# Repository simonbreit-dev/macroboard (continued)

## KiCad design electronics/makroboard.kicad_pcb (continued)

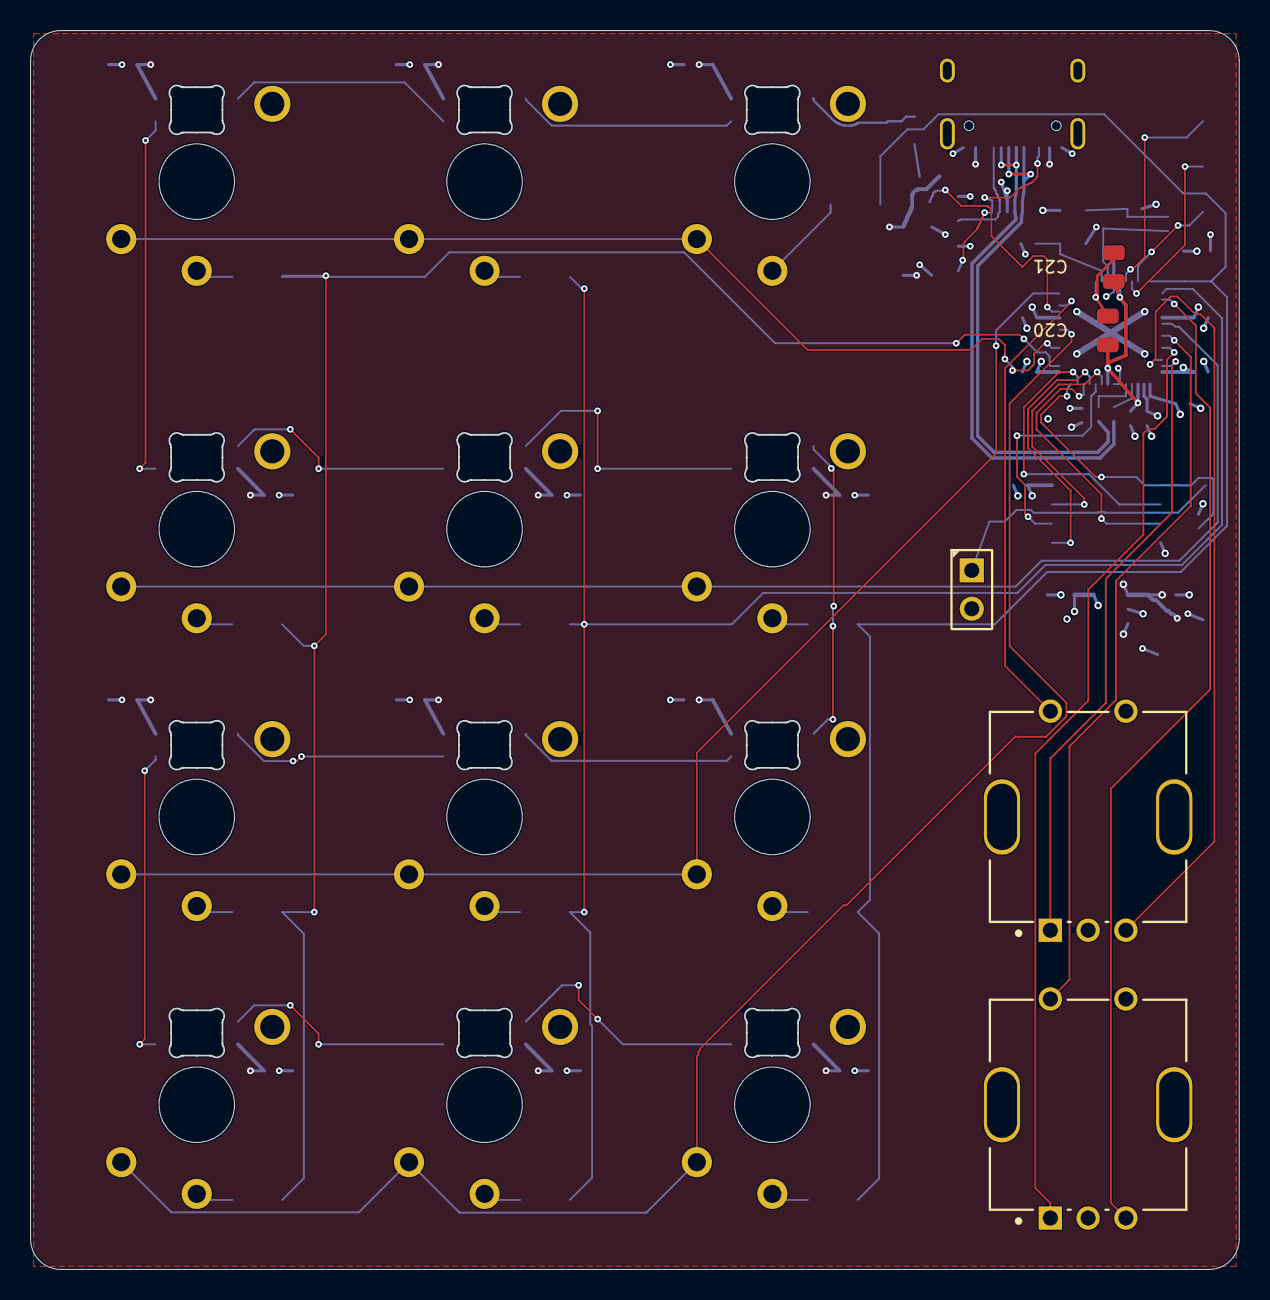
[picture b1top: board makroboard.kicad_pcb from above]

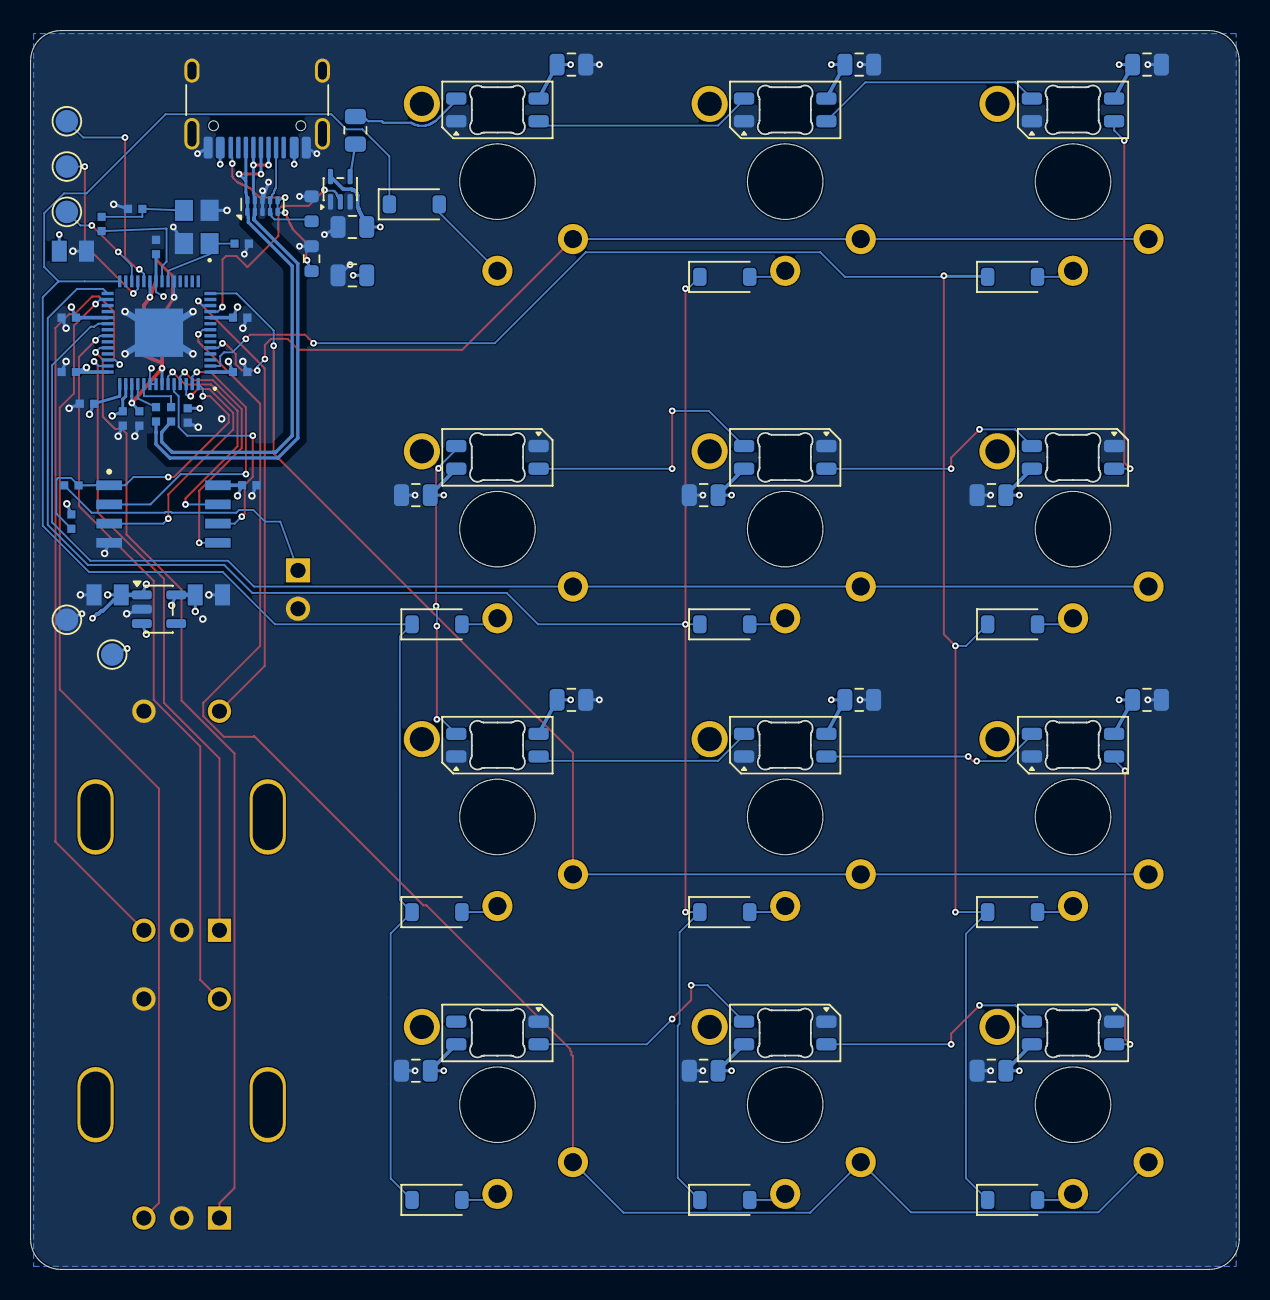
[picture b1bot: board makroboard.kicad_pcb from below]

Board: 4 copper layers, 80.0 x 82.0 mm, 90 parts (73 on the bottom side), 62 nets.

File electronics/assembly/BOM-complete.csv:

Designator,Value,Footprint,MPN,LCSC,Assembly
C1,100nF,Makroboard_PCB:C1_C_0805_2012Metric,CC0805KRX7R9BB104,C49678,Factory
C2,100nF,Makroboard_PCB:C2_C_0805_2012Metric,CC0805KRX7R9BB104,C49678,Factory
C3,100nF,Makroboard_PCB:C3_C_0805_2012Metric,CC0805KRX7R9BB104,C49678,Factory
C4,100nF,Makroboard_PCB:C4_C_0805_2012Metric,CC0805KRX7R9BB104,C49678,Factory
C5,100nF,Makroboard_PCB:C5_C_0805_2012Metric,CC0805KRX7R9BB104,C49678,Factory
C6,100nF,Makroboard_PCB:C6_C_0805_2012Metric,CC0805KRX7R9BB104,C49678,Factory
C7,100nF,Makroboard_PCB:C7_C_0805_2012Metric,CC0805KRX7R9BB104,C49678,Factory
C8,100nF,Makroboard_PCB:C8_C_0805_2012Metric,CC0805KRX7R9BB104,C49678,Factory
C9,100nF,Makroboard_PCB:C9_C_0805_2012Metric,CC0805KRX7R9BB104,C49678,Factory
C10,100nF,Makroboard_PCB:C10_C_0805_2012Metric,CC0805KRX7R9BB104,C49678,Factory
C11,100nF,Makroboard_PCB:C11_C_0805_2012Metric,CC0805KRX7R9BB104,C49678,Factory
C12,100nF,Makroboard_PCB:C12_C_0805_2012Metric,CC0805KRX7R9BB104,C49678,Factory
C13,100nF,Makroboard_PCB:C13_C_0805_2012Metric,CC0805KRX7R9BB104,C49678,Factory
C15,15p,Makroboard_PCB:C15_generic_capc1005x50,0402CG150J500NT,C1548,Factory
C16,15p,Makroboard_PCB:C16_generic_capc1005x50,0402CG150J500NT,C1548,Factory
C17,2.2uF,Makroboard_PCB:C17_generic_capc2012x125,CL21B225KOFNNNE,C28234,Factory
C18,10uF,Makroboard_PCB:C18_generic_capc2012x125,CL21A106KAYNNNE,C15850,Factory
C19,100n,Makroboard_PCB:C19_generic_capc1005x50,CL05B104KO5NNNC,C1525,Factory
C20,100nF,Makroboard_PCB:C20_C_0805_2012Metric,CC0805KRX7R9BB104,C49678,Factory (all-SMD) / required manual Top (one-side)
C21,100nF,Makroboard_PCB:C21_C_0805_2012Metric,CC0805KRX7R9BB104,C49678,Factory (all-SMD) / required manual Top (one-side)
C22,1u,Makroboard_PCB:C22_generic_capc1005x50,CL05A105KA5NQNC,C52923,Factory
C23,100n,Makroboard_PCB:C23_generic_capc1005x50,CL05B104KO5NNNC,C1525,Factory
C24,1u,Makroboard_PCB:C24_generic_capc1005x50,CL05A105KA5NQNC,C52923,Factory
C25,100n,Makroboard_PCB:C25_generic_capc1005x50,CL05B104KO5NNNC,C1525,Factory
C26,100n,Makroboard_PCB:C26_generic_capc1005x50,CL05B104KO5NNNC,C1525,Factory
C27,100n,Makroboard_PCB:C27_generic_capc1005x50,CL05B104KO5NNNC,C1525,Factory
C28,100n,Makroboard_PCB:C28_generic_capc1005x50,CL05B104KO5NNNC,C1525,Factory
C29,100n,Makroboard_PCB:C29_generic_capc1005x50,CL05B104KO5NNNC,C1525,Factory
C30,100n,Makroboard_PCB:C30_generic_capc1005x50,CL05B104KO5NNNC,C1525,Factory
C31,10u,Makroboard_PCB:C31_generic_capc2012x125,CL21A106KAYNNNE,C15850,Factory
C32,2.2uF,Makroboard_PCB:C32_C_0805_2012Metric,CL21B225KOFNNNE,C28234,Factory
D1,SK6812MINI-E,Makroboard_PCB:D1_LED_SK6812MINI-E_3.2x2.8mm_P1.5mm_ReverseMount,SK6812MINI-E,C5149201,Factory
D2,SK6812MINI-E,Makroboard_PCB:D2_LED_SK6812MINI-E_3.2x2.8mm_P1.5mm_ReverseMount,SK6812MINI-E,C5149201,Factory
D3,SK6812MINI-E,Makroboard_PCB:D3_LED_SK6812MINI-E_3.2x2.8mm_P1.5mm_ReverseMount,SK6812MINI-E,C5149201,Factory
D4,SK6812MINI-E,Makroboard_PCB:D4_LED_SK6812MINI-E_3.2x2.8mm_P1.5mm_ReverseMount,SK6812MINI-E,C5149201,Factory
D5,SK6812MINI-E,Makroboard_PCB:D5_LED_SK6812MINI-E_3.2x2.8mm_P1.5mm_ReverseMount,SK6812MINI-E,C5149201,Factory
D6,SK6812MINI-E,Makroboard_PCB:D6_LED_SK6812MINI-E_3.2x2.8mm_P1.5mm_ReverseMount,SK6812MINI-E,C5149201,Factory
D7,SK6812MINI-E,Makroboard_PCB:D7_LED_SK6812MINI-E_3.2x2.8mm_P1.5mm_ReverseMount,SK6812MINI-E,C5149201,Factory
D8,SK6812MINI-E,Makroboard_PCB:D8_LED_SK6812MINI-E_3.2x2.8mm_P1.5mm_ReverseMount,SK6812MINI-E,C5149201,Factory
D9,SK6812MINI-E,Makroboard_PCB:D9_LED_SK6812MINI-E_3.2x2.8mm_P1.5mm_ReverseMount,SK6812MINI-E,C5149201,Factory
D10,SK6812MINI-E,Makroboard_PCB:D10_LED_SK6812MINI-E_3.2x2.8mm_P1.5mm_ReverseMount,SK6812MINI-E,C5149201,Factory
D11,SK6812MINI-E,Makroboard_PCB:D11_LED_SK6812MINI-E_3.2x2.8mm_P1.5mm_ReverseMount,SK6812MINI-E,C5149201,Factory
D12,SK6812MINI-E,Makroboard_PCB:D12_LED_SK6812MINI-E_3.2x2.8mm_P1.5mm_ReverseMount,SK6812MINI-E,C5149201,Factory
D21,1N4148W,Makroboard_PCB:D21_D_SOD-123,1N4148W,C81598,Factory
D22,1N4148W,Makroboard_PCB:D22_D_SOD-123,1N4148W,C81598,Factory
D23,1N4148W,Makroboard_PCB:D23_D_SOD-123,1N4148W,C81598,Factory
D24,1N4148W,Makroboard_PCB:D24_D_SOD-123,1N4148W,C81598,Factory
D25,1N4148W,Makroboard_PCB:D25_D_SOD-123,1N4148W,C81598,Factory
D26,1N4148W,Makroboard_PCB:D26_D_SOD-123,1N4148W,C81598,Factory
D27,1N4148W,Makroboard_PCB:D27_D_SOD-123,1N4148W,C81598,Factory
D28,1N4148W,Makroboard_PCB:D28_D_SOD-123,1N4148W,C81598,Factory
D29,1N4148W,Makroboard_PCB:D29_D_SOD-123,1N4148W,C81598,Factory
D30,1N4148W,Makroboard_PCB:D30_D_SOD-123,1N4148W,C81598,Factory
D31,1N4148W,Makroboard_PCB:D31_D_SOD-123,1N4148W,C81598,Factory
D32,1N4148W,Makroboard_PCB:D32_D_SOD-123,1N4148W,C81598,Factory
D33,TPD4E05U06DQAR,Makroboard_PCB:D33_USON-10_2.5x1.0mm_P0.5mm,TPD4E05U06DQAR,C138714,Factory
J1,TYPE-C-31-M-12,Makroboard_PCB:J1_USB_C_Receptacle_HRO_TYPE-C-31-M-12,TYPE-C-31-M-12,C165948,Factory
J2,TSW-102-07-G-S,Makroboard_PCB:J2_samtec_tsw-102-07-g-s,,,Manual / PCB pad / documentation
PCB1,R3,,,,Manual / PCB pad / documentation
R1,1k,Makroboard_PCB:R1_generic_resc1005x35,0402WGF1001TCE,C11702,Factory
R2,330R,Makroboard_PCB:R2_R_0805_2012Metric,0805W8F3300T5E,C17630,Factory
R3,10k,Makroboard_PCB:R3_generic_resc1005x35,0402WGF1002TCE,C25744,DNP
R4,1k,Makroboard_PCB:R4_generic_resc1005x35,0402WGF1001TCE,C11702,Factory
R5,27,Makroboard_PCB:R5_generic_resc1005x35,0402WGF270JTCE,C25100,Factory
R6,27,Makroboard_PCB:R6_generic_resc1005x35,0402WGF270JTCE,C25100,Factory
R7,5.1k,Makroboard_PCB:R7_R_0603_1608Metric,0603WAF5101T5E,C23186,Factory
R8,5.1k,Makroboard_PCB:R8_R_0603_1608Metric,0603WAF5101T5E,C23186,Factory
SBREV1,S1,,,,Manual / PCB pad / documentation
SW1,SW_Push,Makroboard_PCB:SW1_SW_choc_v2_1u,,,Manual / PCB pad / documentation
SW2,SW_Push,Makroboard_PCB:SW2_SW_choc_v2_1u,,,Manual / PCB pad / documentation
SW3,SW_Push,Makroboard_PCB:SW3_SW_choc_v2_1u,,,Manual / PCB pad / documentation
SW4,SW_Push,Makroboard_PCB:SW4_SW_choc_v2_1u,,,Manual / PCB pad / documentation
SW5,SW_Push,Makroboard_PCB:SW5_SW_choc_v2_1u,,,Manual / PCB pad / documentation
SW6,SW_Push,Makroboard_PCB:SW6_SW_choc_v2_1u,,,Manual / PCB pad / documentation
SW7,SW_Push,Makroboard_PCB:SW7_SW_choc_v2_1u,,,Manual / PCB pad / documentation
SW8,SW_Push,Makroboard_PCB:SW8_SW_choc_v2_1u,,,Manual / PCB pad / documentation
SW9,SW_Push,Makroboard_PCB:SW9_SW_choc_v2_1u,,,Manual / PCB pad / documentation
SW10,SW_Push,Makroboard_PCB:SW10_SW_choc_v2_1u,,,Manual / PCB pad / documentation
SW11,SW_Push,Makroboard_PCB:SW11_SW_choc_v2_1u,,,Manual / PCB pad / documentation
SW12,SW_Push,Makroboard_PCB:SW12_SW_choc_v2_1u,,,Manual / PCB pad / documentation
SW13,RotaryEncoder_Switch,Makroboard_PCB:SW13_Bourns-PEC11R-4220F-S0024-0-0-0,,,Manual / PCB pad / documentation
SW14,RotaryEncoder_Switch,Makroboard_PCB:SW14_Bourns-PEC11R-4220F-S0024-0-0-0,,,Manual / PCB pad / documentation
TP1,TestPoint,Makroboard_PCB:TP1_TestPoint_Pad_D1.5mm,,,Manual / PCB pad / documentation
TP2,TestPoint,Makroboard_PCB:TP2_TestPoint_Pad_D1.5mm,,,Manual / PCB pad / documentation
TP3,TestPoint,Makroboard_PCB:TP3_TestPoint_Pad_D1.5mm,,,Manual / PCB pad / documentation
TP4,TestPoint,Makroboard_PCB:TP4_TestPoint_Pad_D1.5mm,,,Manual / PCB pad / documentation
TP5,TestPoint,Makroboard_PCB:TP5_TestPoint_Pad_D1.5mm,,,Manual / PCB pad / documentation
U1,AP2112K-3.3TRG1,Makroboard_PCB:U1_SOT-23-5,AP2112K-3.3TRG1,C51118,Factory
U2,SN74AHCT1G125DCKR,Makroboard_PCB:U2_SOT-353_SC-70-5,SN74AHCT1G125DCKR,C350557,Factory
U3,W25Q128JVSIQ,Makroboard_PCB:U3_generic_soic127p790x195-8,W25Q128JVSIQ,C97521,Factory
U4,RP2040,Makroboard_PCB:U4_rpi_rp2040_vias,RP2040,C2040,Factory
VARIANT1,RPI-RP2040-MINIMAL,,,,Manual / PCB pad / documentation
X1,12MHz,Makroboard_PCB:X1_generic_xtalcc320x250x80-4,ABM8-272-T3,C20625731,Factory
